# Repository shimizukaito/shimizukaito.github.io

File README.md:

# Codex Portfolio

Shimizu Kaito portfolio site.

## Local update form

Run this command to open the local WORKS update form:

```bash
node scripts/work-form-server.mjs
```

Then open:

```text
http://127.0.0.1:4180/
```

GitHub Pages serves the static files only. The local form is for generating and updating files before committing.

## Homepage styles

The Japanese and English homepages inline only their required CSS to avoid a
render-blocking stylesheet request. `styles.css` remains the source of truth
and is used directly by the other pages. After editing shared styles or homepage
markup, regenerate both inline blocks:

```bash
python3 scripts/build-home-styles.py
```

The generator retains responsive rules and dynamic `dark` / `sketch-frame`
classes. Add any new dynamically created homepage classes to its retained set.

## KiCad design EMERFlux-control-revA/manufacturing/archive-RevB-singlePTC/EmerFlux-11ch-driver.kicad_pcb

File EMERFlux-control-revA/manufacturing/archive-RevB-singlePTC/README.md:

旧Rev.B：TBD3個、PTC1個。新規注文禁止。現行Rev.Cはjlcpcbフォルダ。

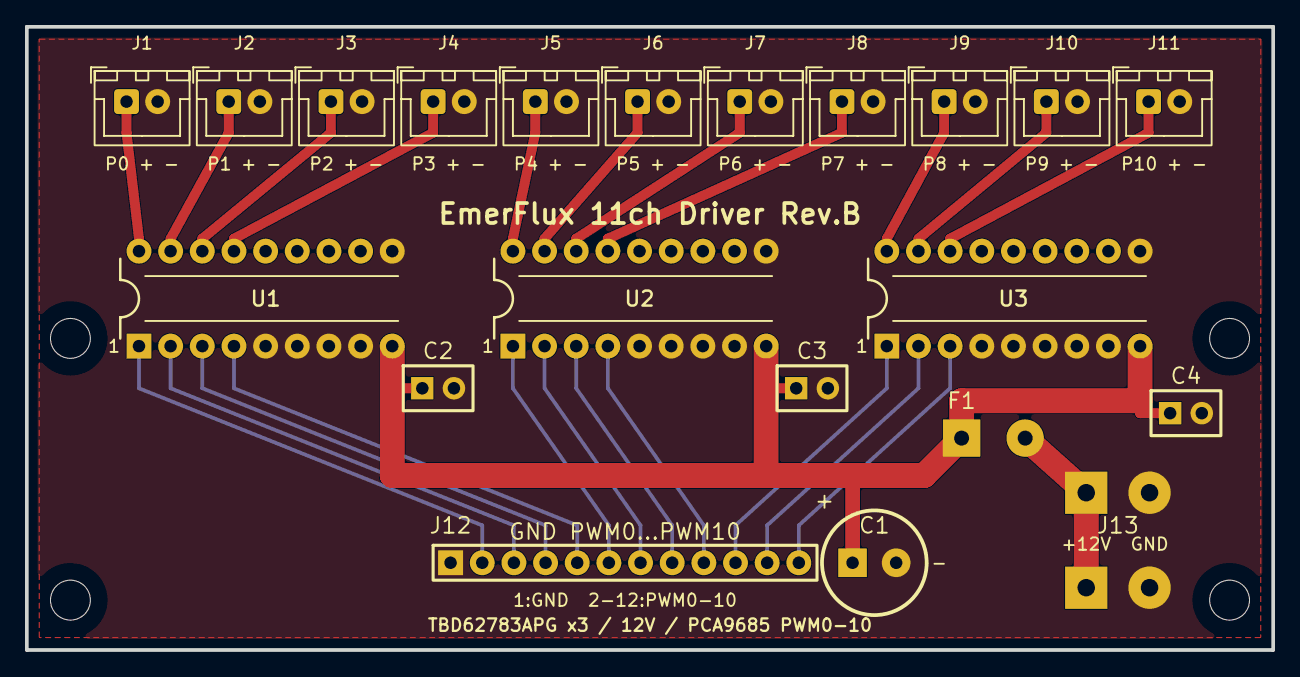
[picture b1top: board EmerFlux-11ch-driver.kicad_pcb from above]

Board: 2 copper layers, 100.0 x 50.0 mm, 25 parts (0 on the bottom side), 25 nets.

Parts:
C1: 25PX470MEFC8X11.5_470uF_25V; Audit_C1
C2: 100nF_U1; Audit_C2
C3: 100nF_U2; Audit_C3
C4: 100nF_U2; Audit_C4
F1: MF-R300_PTC_3A_30V_P5.10mm; Audit_F1
H1: Audit_H1
H2: Audit_H2
H3: Audit_H3
H4: Audit_H4
J1: B2B-XH-A(LF)(SN); Audit_J1
J2: B2B-XH-A(LF)(SN); Audit_J2
J3: B2B-XH-A(LF)(SN); Audit_J3
J4: B2B-XH-A(LF)(SN); Audit_J4
J5: B2B-XH-A(LF)(SN); Audit_J5
J6: B2B-XH-A(LF)(SN); Audit_J6
J7: B2B-XH-A(LF)(SN); Audit_J7
J8: B2B-XH-A(LF)(SN); Audit_J8
J9: B2B-XH-A(LF)(SN); Audit_J9
J10: B2B-XH-A(LF)(SN); Audit_J10
J11: B2B-XH-A(LF)(SN); Audit_J11
J12: PinHeader_1x12_P2.54mm; Audit_J12
J13: WJ142V-5.08-02P-14G-00A; Audit_J13
U1: TBD62783APG; Audit_U1
U2: TBD62783APG; Audit_U2
U3: TBD62783APG; Audit_U3

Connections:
+12V_PROTECTED: C1.1, C2.1, C3.1, C4.1, F1.1, U1.9, U2.9, U3.9
+12V_RAW: F1.2, J13.1
GND: C1.2, C2.2, C3.2, C4.2, J1.2, J2.2, J3.2, J4.2, J5.2, J6.2, J7.2, J8.2, J9.2, J10.2, J11.2, J12.1, J13.2, U1.5, U1.6, U1.7, U1.8, U1.10, U2.5, U2.6, U2.7, U2.8, U2.10, U3.4, U3.5, U3.6, U3.7, U3.8, U3.10
PUMP0_PLUS: J1.1, U1.18
PUMP1_PLUS: J2.1, U1.17
PUMP2_PLUS: J3.1, U1.16
PUMP3_PLUS: J4.1, U1.15
PUMP4_PLUS: J5.1, U2.18
PUMP5_PLUS: J6.1, U2.17
PUMP6_PLUS: J7.1, U2.16
PUMP7_PLUS: J8.1, U2.15
PUMP8_PLUS: J9.1, U3.18
PUMP9_PLUS: J10.1, U3.17
PUMP10_PLUS: J11.1, U3.16
PWM0: J12.2, U1.1
PWM1: J12.3, U1.2
PWM2: J12.4, U1.3
PWM3: J12.5, U1.4
PWM4: J12.6, U2.1
PWM5: J12.7, U2.2
PWM6: J12.8, U2.3
PWM7: J12.9, U2.4
PWM8: J12.10, U3.1
PWM9: J12.11, U3.2
PWM10: J12.12, U3.3

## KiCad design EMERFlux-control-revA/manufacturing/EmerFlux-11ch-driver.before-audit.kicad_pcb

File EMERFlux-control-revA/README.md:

# EmerFlux 11チャンネル行ドライバ基板

現行PCB：manufacturing/EmerFlux-11ch-driver.kicad_pcb。製造資料：manufacturing/jlcpcb/README.md。
100×50mm、2層、FR-4、1.6mm、1oz指定。外付けAE-PCA9685、TBD62783APG×3（4＋4＋3台）。同じ基板11枚で121台。
最終DRC違反0、未配線0。Gerber7層＋ドリル2ファイルを生成・再読込済み。
安全な連続運転・量産は未承認。起動／拘束電流、IC温度、MF-R185×3の評価が必要。最初に1枚だけ実装してください。
旧EasyEDA内蔵PCA9685＋MOSFET案は製造禁止。過去資料はhistoryに保存。before-audit PCBは製造禁止。

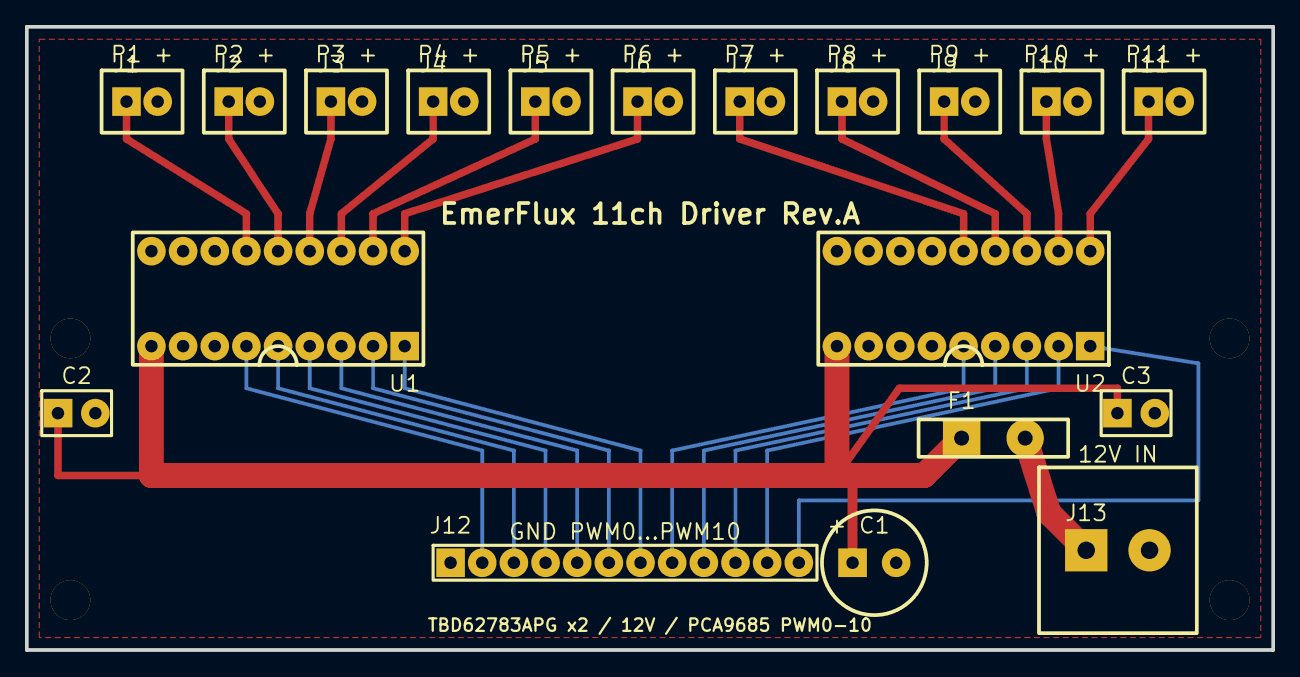
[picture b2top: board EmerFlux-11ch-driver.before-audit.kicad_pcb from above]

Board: 2 copper layers, 100.0 x 50.0 mm, 23 parts (0 on the bottom side), 25 nets.

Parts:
C1: 25PX470MEFC8X11.5_470uF_25V
C2: 100nF_U1
C3: 100nF_U2
F1: MF-R300_PTC_3A_30V_P5.10mm
H1, H2, H3, H4: MountingHole_3.2mm
J1, J2, J3, J4, J5, J6, J7, J8, J9, J10, J11: JST_XH_B2B-XH-A_1x02_P2.50mm
J12: PinHeader_1x12_P2.54mm
J13: WJ142V-5.08-02P-14G-00A
U1, U2: DIP-18_W7.62mm_TBD62783APG

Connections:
+12V_PROTECTED: C1.1, C2.1, C3.1, F1.1, U1.9, U2.9
+12V_RAW: F1.2, J13.1
GND: C1.2, C2.2, C3.2, J1.2, J2.2, J3.2, J4.2, J5.2, J6.2, J7.2, J8.2, J9.2, J10.2, J11.2, J12.1, J13.2, U1.7, U1.8, U1.10, U2.6, U2.7, U2.8, U2.10
PUMP0_PLUS: J1.1, U1.13
PUMP1_PLUS: J2.1, U1.14
PUMP2_PLUS: J3.1, U1.15
PUMP3_PLUS: J4.1, U1.16
PUMP4_PLUS: J5.1, U1.17
PUMP5_PLUS: J6.1, U1.18
PUMP6_PLUS: J7.1, U2.14
PUMP7_PLUS: J8.1, U2.15
PUMP8_PLUS: J9.1, U2.16
PUMP9_PLUS: J10.1, U2.17
PUMP10_PLUS: J11.1, U2.18
PWM0: J12.2, U1.6
PWM1: J12.3, U1.5
PWM2: J12.4, U1.4
PWM3: J12.5, U1.3
PWM4: J12.6, U1.2
PWM5: J12.7, U1.1
PWM6: J12.8, U2.5
PWM7: J12.9, U2.4
PWM8: J12.10, U2.3
PWM9: J12.11, U2.2
PWM10: J12.12, U2.1

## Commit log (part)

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2022-07-07 [テスト]
2022-07-08 [メインビジュアルをcreepynutsぽくした]
2022-07-08 [mvの余白調整と画像差し込み]
2022-07-08 [mvに画像を追加]
2022-07-08 [mvのサイズを調整]
2022-07-08 [worksの画像を丸くしたのとホバーを調整]
2022-07-08 [ファビコンの設定]
2022-07-08 [mvの画像の大きさを調整]
2022-07-08 [タイトル変更]
2022-07-08 [卒研のページを加筆]
2022-07-08 [メールアドレスを変更]
2022-07-10 [iosとandroid用のファビコン画像を追加]
2022-07-10 [OGPの設定を確認]
2022-07-10 [ニコグラフとワークショップのページを修正]
2022-07-10 [一つ前と同じ]
2022-07-11 [ogpの書き換え]
2022-07-11 [変更点]
2022-07-18 [mvの画像を調整]
2023-02-19 [アーカイブの枠を設定]
2023-02-19 [これくらいモデラーを追加]
2023-03-04 worksのファイル名の変更と写真のjpg化
2023-03-09 [ニコグラフの記事を追加]
2023-09-06 新しい構成に変更
2023-09-06 URLを追加
2023-09-07 記事と写真の追加
2023-09-13 URL追加
2023-11-30 プロフィールの追加
2023-12-02 テキスト内容の変更
2023-12-06 worksの写真のCSS変更
2024-02-03 スマホ用のcssを追加とworksの修正
2024-02-03 mVの追加
2024-02-03 タイトルの位置修正
2024-02-23 URLの追加
2024-03-04 worksの追加
2024-03-06 発表歴の追加
2024-03-20 作品の追加
2024-03-23 使用技術の修正
2024-03-23 画像の追加
2024-03-23 URLの修正
2024-10-02 記事の追加
2024-10-03 openprocessingのリンク削除
2024-11-11 バイト先の作品を追加
2025-06-04 以前までのバージョンを一旦削除
2025-06-04 メインページを追加
2025-06-04 一旦削除
2025-06-04 indexのみ
2025-06-04 アブストとコンタクト
2025-06-04 cssとjs
2025-06-04 写真を追加
2025-06-04 ワークスの記事追加
2025-06-04 残りの記事とCSS追加
2025-06-04 さらに追加
2025-06-04 もっと追加
2025-06-05 ワークスを追加
2025-06-11 発表歴を追加
2025-06-11 twistedbandDisplayを追加
2025-06-18 P5のコードを修正
2025-10-29 メインページの画像をリサイズ
2025-11-08 getPostの修正
2025-11-12 記事の文章を修正
2025-11-12 記事を追加
2026-05-26 Replace portfolio structure
2026-05-26 Add imported portfolio media
2026-05-26 Expand works grid width
2026-05-26 作品を追加
2026-05-28 画像参照の変更
2026-05-28 メインの文章を調整
2026-06-03 英語ページの追加
2026-06-20 2026/06/21 ニコグラフインターナショナル２０２６のはっぴょ売れ機を追加
